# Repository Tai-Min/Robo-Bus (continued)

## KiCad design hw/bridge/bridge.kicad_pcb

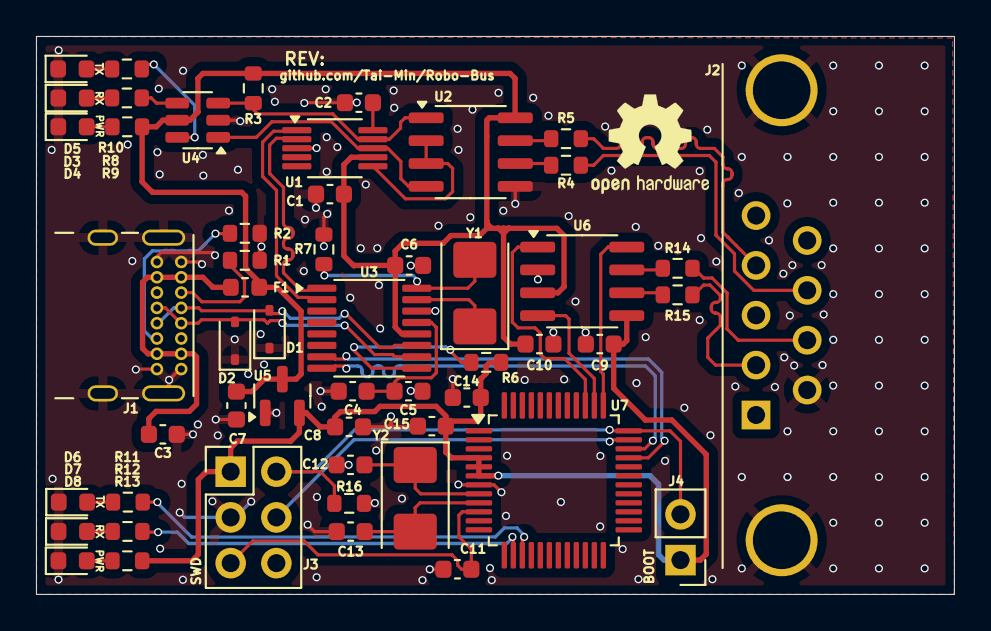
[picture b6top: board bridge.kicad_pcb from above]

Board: 2 copper layers, 51.0 x 31.0 mm, 53 parts (0 on the bottom side), 46 nets.

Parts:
C1, C2, C5, C9, C10, C11, C14, C15: 100n; C_0603_1608Metric
C3: 10n; C_0603_1608Metric
C4, C7, C8: 10u; C_0603_1608Metric
C6: 1u; C_0603_1608Metric
C12, C13: 6p; C_0603_1608Metric
D1, D2: PTVSHC3D4V5B; D_SOD-323
D3, D4, D6, D7: yellow; LED_0603_1608Metric
D5, D8: green; LED_0603_1608Metric
F1: 500mA; Fuse_0603_1608Metric
J1: USB_C_Receptacle_USB2.0_14P; USB_C_Receptacle_GCT_USB4085
J2: DE9; DSUB-9_Pins_Horizontal_P2.77x2.84mm_EdgePinOffset7.70mm_Hou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
J3: SWD; PinHeader_2x03_P2.54mm_Vertical
J4: BOOT; PinHeader_1x02_P2.54mm_Vertical
R1, R2: 5.1K; R_0603_1608Metric
R3, R6, R16: 10K; R_0603_1608Metric
R4, R5, R7, R14, R15: 0R; R_0603_1608Metric
R8, R9, R10, R11, R12, R13: 1K; R_0603_1608Metric
U1: CH340E; MSOP-10_3x3mm_P0.5mm
U2: MAX485E; SOIC-8_3.9x4.9mm_P1.27mm
U3: CH334R; QSOP-16_3.9x4.9mm_P0.635mm
U4: 74LVC2G04; SOT-23-6
U5: MCP1754S-3302xCB; SOT-23
U6: TJA1051T-3; SOIC-8_3.9x4.9mm_P1.27mm
U7: STM32G0B1CBT; LQFP-48_7x7mm_P0.5mm
Y1: HCI XC53G2-12.000-F20LJDT; Crystal_SMD_5032-2Pin_5.0x3.2mm
Y2: HCI XC53G2-8.000-F12NJHP; Crystal_SMD_5032-2Pin_5.0x3.2mm

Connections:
+3.3V: C8.2, C9.2, C14.2, C15.2, J3.1, J4.1, R6.2, R13.2, U5.2 (VO), U6.5 (VIO), U7.4 (VBAT), U7.5 (VREF+), U7.6 (VDD)
+5V: C1.2, C6.2, C7.2, C10.2, F1.2, R3.1, R10.2, U1.7 (VCC), U2.8 (VCC), U3.12 (V5), U4.5 (VCC), U5.3 (VI), U6.3 (VCC)
/CAN+: J2.7, R14.1
/CAN-: J2.2, R15.1
/D+: D1.2 (A2), J1.A6 (D+), J1.B6 (D+), U3.11 (DPU+)
/D-: D2.2 (A2), J1.A7 (D-), J1.B7 (D-), U3.10 (DMU-)
/D_CAN+: U3.8 (DP1+), U7.34 (PA10/PA12)
/D_CAN-: U3.7 (DM1-), U7.33 (PA9/PA11)
/D_RS+: U1.1 (UD+), U3.2 (DP4+)
/D_RS-: U1.2 (UD-), U3.1 (DM4-)
/MODBUS+: J2.8, R4.1
/MODBUS-: J2.4, R5.1
/RX: R3.2, U1.9 (RXD), U2.1 (RO), U4.3
/TX: U1.8 (TXD), U2.4 (DI), U4.1
/VUSB: C3.2, F1.1, J1.A4 (VBUS), J1.A9 (VBUS), J1.B4 (VBUS), J1.B9 (VBUS)
/mcu/CAN_RX: U6.4 (RXD), U7.38 (PD0)
/mcu/CAN_S: U6.8 (S), U7.37 (PA15)
/mcu/CAN_TX: U6.1 (TXD), U7.39 (PD1)
/mcu/LED_RX: R12.2, U7.14 (PA3)
/mcu/LED_TX: R11.2, U7.15 (PA4)
/mcu/NRST: C11.2, J3.5, U7.10 (PF2)
/mcu/SWCLK: J3.2, J4.2, R16.1, U7.36 (PA14)
/mcu/SWDIO: J3.4, U7.35 (PA13)
GND: C1.1, C2.2, C3.1, C4.1, C5.1, C6.1, C7.1, C8.1, C9.1, C10.1, C11.1, C12.1, C13.1, C14.1, C15.1, D1.1 (A1), D2.1 (A1), D3.1 (K), D4.1 (K), D5.1 (K), D6.1 (K), D7.1 (K), D8.1 (K), J1.A1 (GND), J1.A12 (GND), J1.B1 (GND), J1.B12 (GND), J1.S1 (SHIELD), J2.0 (PAD), J2.3, J2.6, J3.3, R1.2, R2.2, R7.2, R16.2, U1.3 (GND), U2.5 (GND), U3.14 (GND), U4.2 (GND), U5.1 (GND), U6.2 (GND), U7.7 (VSS)
unnamed: D3.2 (A), R8.1
unnamed: D4.2 (A), R9.1
unnamed: D5.2 (A), R10.1
unnamed: D6.2 (A), R11.1
unnamed: D7.2 (A), R12.1
unnamed: D8.2 (A), R13.1
unnamed: J1.A5 (CC1), R1.1
unnamed: J1.B5 (CC2), R2.1
unnamed: R8.2, U4.6
unnamed: R9.2, U4.4
unnamed: U1.6 (TNOW), U2.2 (~RE), U2.3 (DE)
unnamed: C2.1, U1.10 (V3)
unnamed: R4.2, U2.6 (A)
unnamed: R5.2, U2.7 (B)
unnamed: C4.2, C5.2, U3.13 (VDD33)
unnamed: R7.1, U3.16 (XI), Y1.2
unnamed: U3.15 (XO), Y1.1
unnamed: R6.1, U3.9 (~RESET/CDP)
unnamed: R14.2, U6.7 (CANH)
unnamed: R15.2, U6.6 (CANL)
unnamed: C12.2, U7.8 (PF0), Y2.1
unnamed: C13.2, U7.9 (PF1), Y2.2

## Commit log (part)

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2025-11-10 Add local runner action dummy
2025-11-10 Add local runner action
    Add action to verify whether commit author in a PR is a collaborator.
    This action in the future shall be used to run checks on a local runner, for now it only prints collaborator status.
2025-11-10 Test
2025-11-10 aTest
2025-11-10 Add reusable workflow for committer check
2025-11-10 Remove workflow dispatch from local_runner_CI
2025-11-10 Add check_head_branch.yml
2025-11-10 Actions cleanup
2025-11-10 Add KiCad gitignore
2025-11-10 Add basic KiCad action
2025-11-10 Cleanup actions
2025-11-11 hardware_checks.yml now runs as needed
2025-11-11 Fix permissions for branch name enforcer
2025-11-11 Add blank canbus/rs485 terminator project Add blank mcu project
2025-11-11 Add diagram for bus connector PCB Change labeler.yml
2025-11-12 Add initial bus connector schematic
2025-11-13 Change action triggers
2025-11-13 Add logs to signoff checker
2025-11-13 Add connector board WIP
2025-11-13 Add test layout to connector PCB
2025-11-13 Simplify local_runner_CI
2025-11-13 Remove empty line
2025-11-13 Add echo
2025-11-13 Edit actions
2025-11-14 Add artifacts to hardware checks
2025-11-14 AUTO: Update reports
2025-11-14 Fix issues with bus connector project
2025-11-14 Fix bus connector errors
2025-11-14 Finish connector prototype
2025-11-14 Finish bus connector prototype
2025-11-17 Fix hardware checks comment for forks
2025-11-18 Final bus connector prototype from Tai-Min
2025-11-20 Add usb - modbus bridge
2025-11-20 Add USB to RS485/CAN bridge sch
2025-11-20 Fix schematic labels
2025-11-20 Remove obsolete shield label
2025-11-20 Fix parity issues
2025-11-20 Add bus protection, change db9 types
2025-11-20 Add initial PCB to the bridge
2025-11-20 Fix jumpers
2025-11-21 Simplify bus connector
2025-11-22 Redesign the PCB, remove DNP components
2025-11-22 Add datasheets, add BOM links
2025-11-22 Fix missing schematic header
2025-11-23 Minor fixes
2025-11-24 Add hub crystal-free alternative, add hub rst pull up, replace usbc with tht alternative
2025-11-24 Fix annotation error
2025-11-24 Update runner to remove old bot comments
2025-11-24 Add token
2025-11-24 Add magic header
2025-11-24 Add comment_remover action
2025-11-24 Fix input for pr_commenter
2025-11-24 Update LICENSE
2025-11-24 Create LICENSE
2025-11-24 Add license
2025-11-24 Manufacture fixes
2025-11-24 Add dsub datasheet
2025-11-24 Add datasheets, minor pcb changes
2025-11-24 Add docs
2025-11-24 Fix silkscreen, fix thermal error, add via array
2025-11-24 Fix silkscreen
2025-11-24 Tracks for left panel rerouted, tvs diode replaced, more vias added
2025-11-24 Change layer of the license
2025-12-01 Add QR code, remove shield jumper
2025-12-01 Remove Logos lib, fix committer check
2025-12-01 Add test points
2025-12-02 Change versioning
2025-12-02 Redo vias and VCC
2025-12-02 Minor changes
2025-12-03 Add board2pdf
2025-12-03 Add checkout action to PR alerts workflow
2025-12-03 Add create hw release action
2025-12-03 Add missing checkout
2025-12-03 Add proper drawing sheet with license
2025-12-03 Add release publisher
2025-12-03 Fix condition to check for release command
2025-12-03 Refactor condition for release command check
2025-12-03 Fix assignees format in release success issue template
2025-12-03 Fix assignees syntax in release failure issue template
2025-12-03 Quote github.actor in create_hw_release.yml
2025-12-03 Remove AUTHOR variable from create_hw_release.yml
    Removed the AUTHOR variable from the workflow.
2025-12-03 Update assignee to use context actor in issue template
2025-12-03 Update assignees field in release success issue
2025-12-03 Update ISSUE_HW_RELEASE_SUCCESS.md template
2025-12-03 Remove assignees from release failure issue template
    Removed assignees field from the automated release issue template.
2025-12-03 Add assignees to success and failure issue creation
2025-12-03 Update LCSC BOM
2025-12-03 Update datasheets
2025-12-03 Add jumpers and test points, add QR code
2025-12-03 Add gnd test point
2025-12-05 Cleanup
2025-12-05 Fix parity issue
2025-12-06 Add shield files
2025-12-06 WIP shield
2025-12-08 Fix datasheet links, remove DNP from TVS
2025-12-09 Redesign VCC trace
2025-12-09 Change revision to 1.0.1d
2025-12-09 Add 5V TP, Cleanup
2025-12-09 Add LED jumper
2025-12-09 Minor PCB fixes
2025-12-09 USB_BRIDGE: Add readme with credits
2025-12-16 Update repository reference in release publisher workflow
2026-01-27 Update KiCad installation to latest version
2026-01-27 Replace USB-C TVS with working ones, replace footprint of TVS to hand solder version
2026-01-27 Change usb bridge revision
2026-01-27 Update KiCad installation to use latest version
2026-01-28 usb_bridge: Replace invalid TVS datasheet
2026-02-03 usb_bridge: Replace LCSC part codes for USB TVS diodes
2026-02-14 usb_bridge: Major LED fixes, replace USB-C protection circuit, add RS485 pullups, add mounting holes
2026-03-10 Remove residual silkscreen from the bottom, replace LED resistor to 10K
2026-03-23 Add PyMuPDF installation to hardware checks workflow
2026-03-23 Downgrade PyMuPDF version to 1.13.20
2026-03-23 Upgrade PyMuPDF version to 1.24.13
2026-03-23 Add Pico expansion board
2026-03-23 Install PyMuPDF version 1.24.13
    Add specific version installation for PyMuPDF.
